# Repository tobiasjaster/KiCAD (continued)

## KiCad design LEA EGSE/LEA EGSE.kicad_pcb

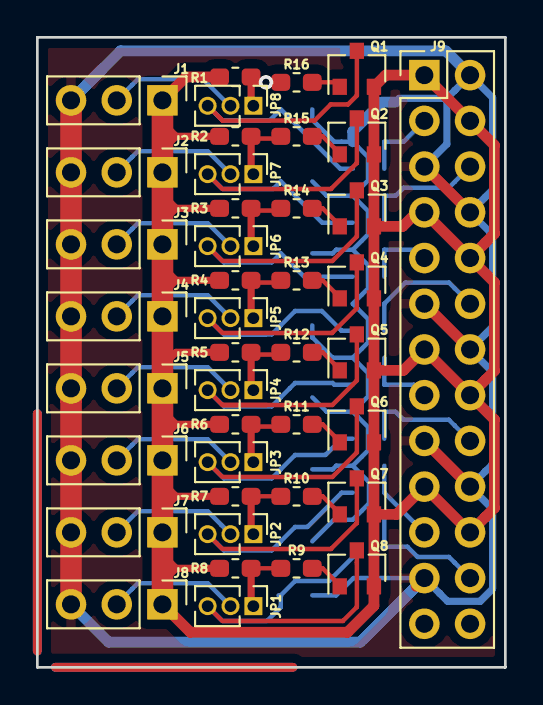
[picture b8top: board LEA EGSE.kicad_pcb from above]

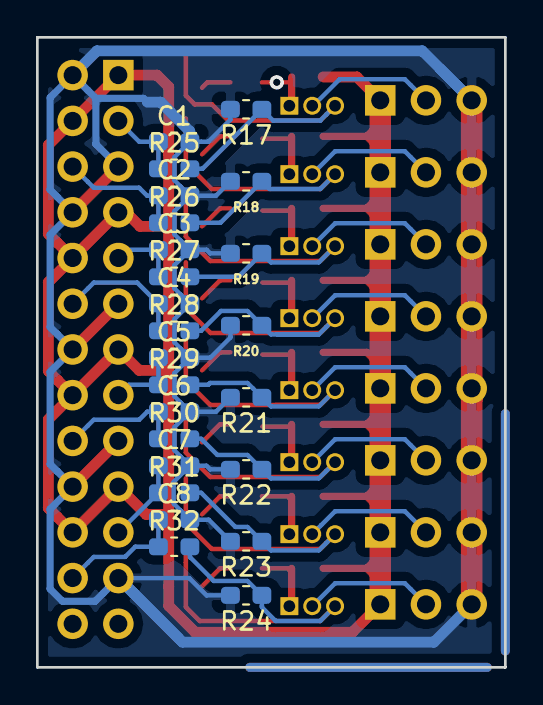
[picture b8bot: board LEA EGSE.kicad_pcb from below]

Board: 4 copper layers, 26.0 x 35.0 mm, 65 parts (24 on the bottom side), 42 nets.

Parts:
C1, C2, C3, C4, C5, C6, C7, C8: 1uF; C_0603_1608Metric_Pad1.05x0.95mm_HandSolder
J1, J2, J3, J4, J5, J6, J7, J8: Conn_01x03; PinHeader_1x03_P2.54mm_Vertical
J9: Conn_02x13_Odd_Even; PinHeader_2x13_P2.54mm_Vertical
JP1, JP2, JP3, JP4, JP5, JP6, JP7, JP8: Jumper_3_Open; PinHeader_1x03_P1.27mm_Vertical
Q1, Q2, Q3, Q4, Q5, Q6, Q7, Q8: BC857; SOT-23
R1, R2, R3, R4, R5, R6, R7, R8, R17, R18, R19, R20, R21, R22, R23, R24: 47k; R_0603_1608Metric_Pad1.05x0.95mm_HandSolder
R9, R10, R11, R12, R13, R14, R15, R16: 2k; R_0603_1608Metric_Pad1.05x0.95mm_HandSolder
R25, R26, R27, R28, R29, R30, R31, R32: 1k; R_0603_1608Metric_Pad1.05x0.95mm_HandSolder

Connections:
+5V: J1.1, J2.1, J3.1, J4.1, J5.1, J6.1, J7.1, J8.1, J9.1, J9.4, J9.7, J9.10, J9.13, J9.16, J9.19, J9.22, Q1.2, Q2.2, Q3.2, Q4.2, Q5.2, Q6.2, Q7.2, Q8.2, R1.1, R2.1, R3.1, R4.1, R5.1, R6.1, R7.1, R8.1
GND: C1.2, C2.2, C3.2, C4.2, C5.2, C6.2, C7.2, C8.2, J1.3, J2.3, J3.3, J4.3, J5.3, J6.3, J7.3, J8.3, J9.2, J9.5, J9.8, J9.11, J9.14, J9.17, J9.20, J9.23, R17.2, R18.2, R19.2, R20.2, R21.2, R22.2, R23.2, R24.2
unnamed: C1.1, J9.3, R25.1
unnamed: C2.1, J9.6, R26.1
unnamed: C3.1, J9.9, R27.1
unnamed: C4.1, J9.12, R28.1
unnamed: C5.1, J9.15, R29.1
unnamed: C6.1, J9.18, R30.1
unnamed: C7.1, J9.21, R31.1
unnamed: C8.1, J9.24, R32.1
unnamed: J1.2, JP8.2
unnamed: J2.2, JP7.2
unnamed: J3.2, JP6.2
unnamed: J4.2, JP5.2
unnamed: J5.2, JP4.2
unnamed: J6.2, JP3.2
unnamed: J7.2, JP2.2
unnamed: J8.2, JP1.2
unnamed: JP1.1, R8.2, R9.2
unnamed: JP1.3, Q8.3, R24.1, R32.2
unnamed: JP2.1, R7.2, R10.2
unnamed: JP2.3, Q7.3, R23.1, R31.2
unnamed: JP3.1, R6.2, R11.2
unnamed: JP3.3, Q6.3, R22.1, R30.2
unnamed: JP4.1, R5.2, R12.2
unnamed: JP4.3, Q5.3, R21.1, R29.2
unnamed: JP5.1, R4.2, R13.2
unnamed: JP5.3, Q4.3, R20.1, R28.2
unnamed: JP6.1, R3.2, R14.2
unnamed: JP6.3, Q3.3, R19.1, R27.2
unnamed: JP7.1, R2.2, R15.2
unnamed: JP7.3, Q2.3, R18.1, R26.2
unnamed: JP8.1, R1.2, R16.2
unnamed: JP8.3, Q1.3, R17.1, R25.2
unnamed: Q1.1, R16.1
unnamed: Q2.1, R15.1
unnamed: Q3.1, R14.1
unnamed: Q4.1, R13.1
unnamed: Q5.1, R12.1
unnamed: Q6.1, R11.1
unnamed: Q7.1, R10.1
unnamed: Q8.1, R9.1

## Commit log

2019-07-08 Initial DataLogger
2019-07-08 Initial LEA EGSE
2019-07-08 Initial Homeautomation
2019-07-10 Update HA Files Homeautomation: Add 3V3A to Ethernet Connector
2019-09-09 Change PowerDCDC
